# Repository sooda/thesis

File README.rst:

Multi-view stereo reconstruction for computer graphics content capture
======================================================================

Hello, this is my master's thesis work titled as above, and contains both the thesis text itself and some source code and electrical schematics developed during the work in Aalto University in 2014-2015.
For the occasional gibberish, consult a Finnish dictionary.
The technical "multi-view stereo reconstruction" is sometimes called "3D scanning": digitizing real-life object geometry from multiple photographs.
The practical work in this thesis was about building a rig for that purpose.
No reconstruction programs were written, unfortunately.
Try e.g. VisualSFM_ and MeshLab_ for that.

.. _VisualSFM: http://ccwu.me/vsfm/
.. _MeshLab: http://meshlab.sourceforge.net/

.. image:: latex/gfx/bitmap/setupcams.jpg
   :width: 500px
   :alt: camera array

.. image:: latex/gfx/bitmap/horsereconst.jpg
   :width: 500px
   :alt: horse mask rendering

Code
----

The thesis talks also about the background math, but the only code here is for controlling DSLRs remotely using gPhoto2_ in C++ and some shell scripts.
The tools were only tested using nine Canon EOS 700D cameras; no guarantees are given for others, but not much major changes are expected to be required.
I forgot to run valgrind on the final tool, so expect no warranty in memory leaks or any other errors.

.. _gPhoto2: http://gphoto.org/

The code here represents a prototype only, but it works for what was required, it's just not very polished.
I wrote a C++ wrapper for gphoto that is unimaginatively called *gpwrap*.
A preview tool (*gphotogrid*) downloads a live stream from each camera in parallel and allows the user to configure their parameters (aperture and such), with no significant performance optimizations or anything, as it's just a proof of concept.
The wrapper and the grid have been tested to work in recent versions of Linux and Mac OS X using the EOS 700Ds, but YMMV.
A more polished tool called `CaptureQuick`_ is developed on top of it by Daniel Thul; if you are going to use the wrapper for developing your own programs, or want the grid tool, look there too.
CaptureQuick still uses the wrapper written by me with only minor modifications (as of June 2015).
Expect it to grow further.

.. _CaptureQuick: https://github.com/dthul/capture-quick

.. image:: latex/gfx/bitmap/gphotogrid.png
   :width: 500px
   :alt: gphotogrid

Electronics
-----------

I built a simple remote tool for controlling the shutters of the nine cameras via a single usb-serial connection, in `arbitrary order`_ (typically simultaneously, though).
The control output goes directly to the 700Ds' shutter release inputs (a 2.5mm stereo jack).
The box has also a button for human interaction, and it's based on Nucleo-F401RE_, a simple STM32 board.
The schematics and the PCB are in EAGLE_ 7.0.0 format.
I named the thing *camsremote*.
No warranty.

.. _arbitrary order: https://www.youtube.com/watch?v=bDDnQzyOaFg
.. _Nucleo-F401RE: http://www.st.com/nucleoF401RE-pr
.. _EAGLE: http://www.cadsoftusa.com/eagle-pcb-design-software/

.. image:: latex/gfx/bitmap/camsremote.jpg
   :width: 500px
   :alt: remote trigger tool

Abstract
--------

Rendering of photorealistic models is becoming increasingly feasible and important in computer graphics.
Due to the high amount of work in creating such models by hand, required by the need of high level of detail in geometry, colors, and animation, it is desirable to automate the model creation.
This task is realised by recovering content from photographs that describe the modeled subject from multiple viewpoints.
In this thesis, elementary theory on image acquisition and photograph-based reconstruction of geometry and colors is studied and recent research and software for graphics content reconstruction are reviewed.
Based on the studied background, a rig is built as a grid of nine off-the-shelf digital cameras, a custom remote shutter trigger, and supporting software.
The purpose of the rig is to capture high-quality photographs and video in a reliable and practical manner, to be processed in multi-view reconstruction programs.

The camera rig was configured to shoot small static subjects for experiments.
The resulting photos and video were then processed directly for the subject's geometry and color, with little or no image enhancements done.
Two typical reconstruction software pipelines were described and tested.
The rig was found to perform well for several subjects with little subject-specific tuning;
issues in the setup were analyzed and further improvements suggested based on the captured test models.
Image quality of the cameras was found to be excellent for the task, and most problems arose from uneven lighting and practical issues.
The developed rig was found to produce sub-millimeter scale accuracy in geometry and texture of subjects such as human faces.
Future work was suggested for lighting, video synchronization and study of state-of-the-art image processing and reconstruction algorithms.

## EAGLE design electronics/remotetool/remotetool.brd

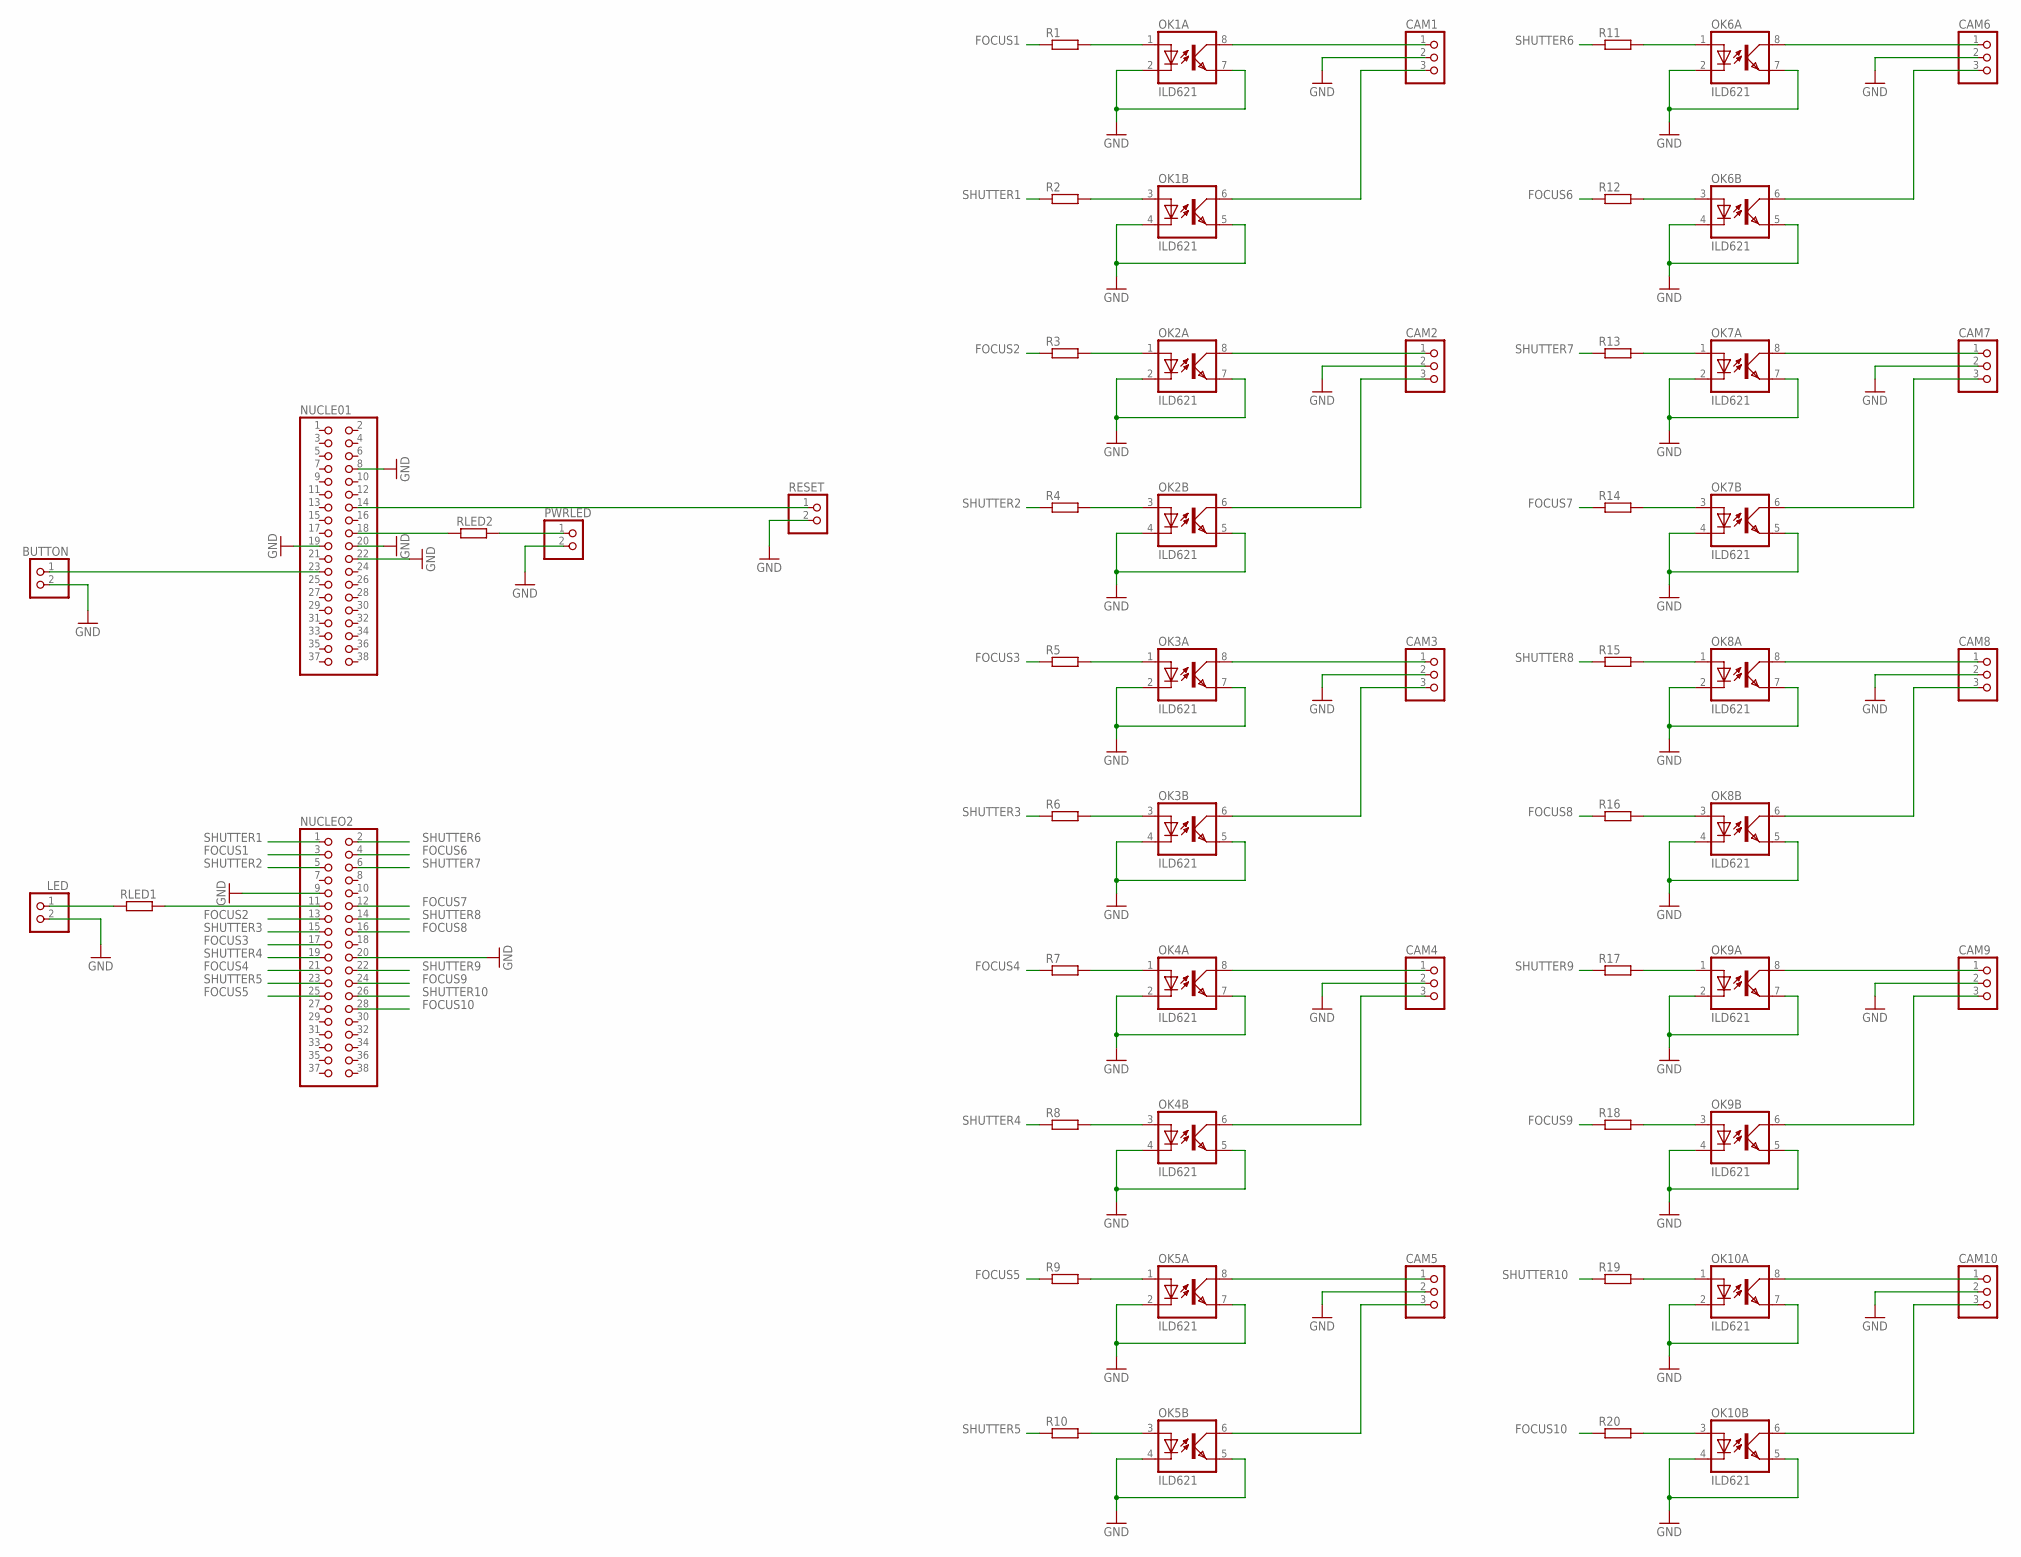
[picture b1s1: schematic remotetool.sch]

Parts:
BUTTON: PINHD-1X2; 1X02
CAM1, CAM2, CAM3, CAM4, CAM5, CAM6, CAM7, CAM8, CAM9, CAM10: PINHD-1X3; 1X03
LED: PINHD-1X2; 1X02
NUCLE01: PINHD-2X19; 2X19
NUCLEO2: PINHD-2X19; 2X19
OK1, OK2, OK3, OK4, OK5, OK6, OK7, OK8, OK9, OK10: ILD621; DIL08
PWRLED: PINHD-1X2; 1X02
R1, R2, R3, R4, R5, R6, R7, R8, R9, R10, R11, R12, R13, R14, R15, R16, R17, R18, R19, R20: R-EU_0207/2V; 0207/2V
RESET: PINHD-1X2; 1X02
RLED1, RLED2: R-EU_0207/2V; 0207/2V

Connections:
FOCUS1: NUCLEO2.3, R1.1
FOCUS2: NUCLEO2.13, R3.1
FOCUS3: NUCLEO2.17, R5.1
FOCUS4: NUCLEO2.21, R7.1
FOCUS5: NUCLEO2.25, R9.1
FOCUS6: NUCLEO2.4, R12.1
FOCUS7: NUCLEO2.12, R14.1
FOCUS8: NUCLEO2.16, R16.1
FOCUS9: NUCLEO2.24, R18.1
FOCUS10: NUCLEO2.28, R20.1
GND: BUTTON.2, CAM1.2, CAM2.2, CAM3.2, CAM4.2, CAM5.2, CAM6.2, CAM7.2, CAM8.2, CAM9.2, CAM10.2, LED.2, NUCLE01.8, NUCLE01.19, NUCLE01.20, NUCLE01.22, NUCLEO2.9, NUCLEO2.20, OK1.2 (C), OK1.4 (C), OK1.5 (EMIT), OK1.7 (EMIT), OK2.2 (C), OK2.4 (C), OK2.5 (EMIT), OK2.7 (EMIT), OK3.2 (C), OK3.4 (C), OK3.5 (EMIT), OK3.7 (EMIT), OK4.2 (C), OK4.4 (C), OK4.5 (EMIT), OK4.7 (EMIT), OK5.2 (C), OK5.4 (C), OK5.5 (EMIT), OK5.7 (EMIT), OK6.2 (C), OK6.4 (C), OK6.5 (EMIT), OK6.7 (EMIT), OK7.2 (C), OK7.4 (C), OK7.5 (EMIT), OK7.7 (EMIT), OK8.2 (C), OK8.4 (C), OK8.5 (EMIT), OK8.7 (EMIT), OK9.2 (C), OK9.4 (C), OK9.5 (EMIT), OK9.7 (EMIT), OK10.2 (C), OK10.4 (C), OK10.5 (EMIT), OK10.7 (EMIT), PWRLED.2, RESET.2
unnamed: OK1.1 (A), R1.2
unnamed: OK1.3 (A), R2.2
unnamed: CAM1.1, OK1.8 (COL)
unnamed: CAM1.3, OK1.6 (COL)
unnamed: OK2.1 (A), R3.2
unnamed: OK2.3 (A), R4.2
unnamed: CAM2.1, OK2.8 (COL)
unnamed: CAM2.3, OK2.6 (COL)
unnamed: OK3.1 (A), R5.2
unnamed: OK3.3 (A), R6.2
unnamed: CAM3.1, OK3.8 (COL)
unnamed: CAM3.3, OK3.6 (COL)
unnamed: OK4.1 (A), R7.2
unnamed: OK4.3 (A), R8.2
unnamed: CAM4.1, OK4.8 (COL)
unnamed: CAM4.3, OK4.6 (COL)
unnamed: OK5.1 (A), R9.2
unnamed: OK5.3 (A), R10.2
unnamed: CAM5.1, OK5.8 (COL)
unnamed: CAM5.3, OK5.6 (COL)
unnamed: OK6.1 (A), R11.2
unnamed: OK6.3 (A), R12.2
unnamed: CAM6.1, OK6.8 (COL)
unnamed: CAM6.3, OK6.6 (COL)
unnamed: OK7.1 (A), R13.2
unnamed: OK7.3 (A), R14.2
unnamed: CAM7.1, OK7.8 (COL)
unnamed: CAM7.3, OK7.6 (COL)
unnamed: OK8.1 (A), R15.2
unnamed: OK8.3 (A), R16.2
unnamed: CAM8.1, OK8.8 (COL)
unnamed: CAM8.3, OK8.6 (COL)
unnamed: OK9.1 (A), R17.2
unnamed: OK9.3 (A), R18.2
unnamed: CAM9.1, OK9.8 (COL)
unnamed: CAM9.3, OK9.6 (COL)
unnamed: OK10.1 (A), R19.2
unnamed: OK10.3 (A), R20.2
unnamed: CAM10.1, OK10.8 (COL)
unnamed: CAM10.3, OK10.6 (COL)
unnamed: NUCLEO2.11, RLED1.2
unnamed: BUTTON.1, NUCLE01.23
unnamed: NUCLE01.14, RESET.1
unnamed: LED.1, RLED1.1
unnamed: NUCLE01.18, RLED2.2
unnamed: PWRLED.1, RLED2.1
SHUTTER1: NUCLEO2.1, R2.1
SHUTTER2: NUCLEO2.5, R4.1
SHUTTER3: NUCLEO2.15, R6.1
SHUTTER4: NUCLEO2.19, R8.1
SHUTTER5: NUCLEO2.23, R10.1
SHUTTER6: NUCLEO2.2, R11.1
SHUTTER7: NUCLEO2.6, R13.1
SHUTTER8: NUCLEO2.14, R15.1
SHUTTER9: NUCLEO2.22, R17.1
SHUTTER10: NUCLEO2.26, R19.1

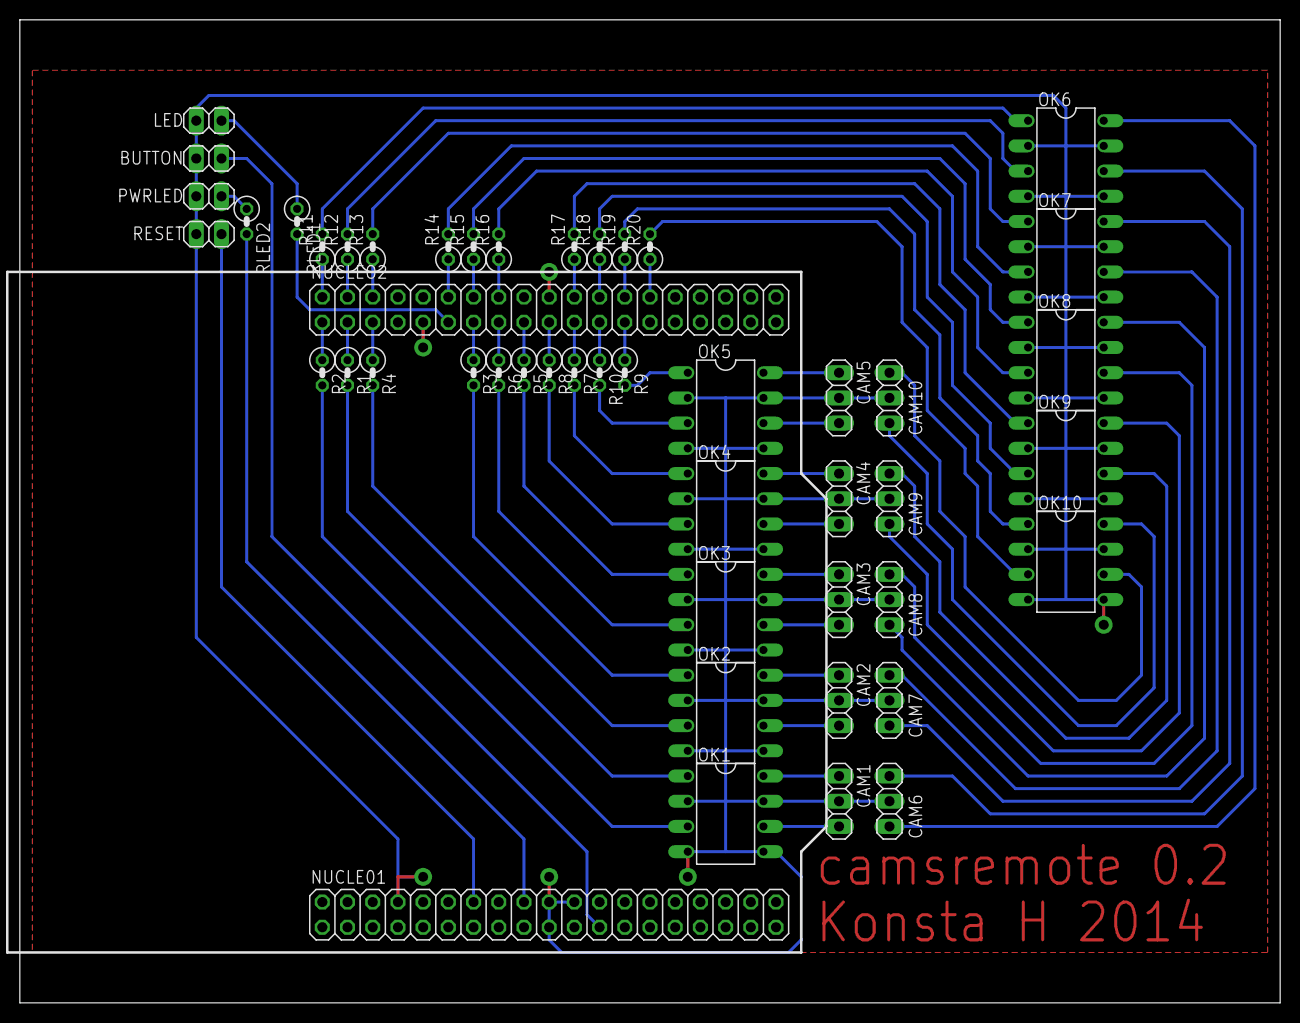
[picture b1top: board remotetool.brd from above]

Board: 2 copper layers, 127.0 x 99.1 mm, 48 parts (0 on the bottom side), 67 nets.

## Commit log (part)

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2014-01-14 initial commit
    Basic modular structure based on the aalto thesis template.
2014-01-31 notes of first three weeks
2014-02-04 opencv example pics, wxwidgets testing to display
2014-02-17 initial latex content, note update
2014-04-14 initial seminar work copypasta
2014-04-15 seminar work updates
2014-04-16 a little about video and imaging
2014-04-17 refactor calib/transform sec
2014-04-18 haaaaaaaaands
2014-04-24 last seminar presis tweaks
2014-04-24 kameraostossuunnitelma
2014-05-02 src: list of all cameras from gphoto
2014-05-02 src: gphoto grid previewer
2014-05-02 gpgrid: also shutter speed slider
2014-05-02 gpwrap: also test iso
2014-05-02 gpgrid: optionspanel hifi; text and padding
2014-05-05 gpgrid: timeline control
    sweet tracks of points on a scrollable and zoomable timeline
2014-05-06 gprid: timeline autoscrolling to follow insertions
2014-05-08 gpgrid: numcams() for app
    no more cams.size() sprinkled randomly everywhere
2014-05-09 gpgrid: change optionspanel wxsliders to wxchoices
    because text in a dropdown list is much better
2014-05-09 gpwrap: remember timeline follow when reseting it
    slight bugfix for when new cameras resets the timeline
2014-05-16 kamerajalustojen ostoslistamuistiinpanot
2014-05-24 tex: light refactor, initial implementation text
2014-05-24 tex: imaging, pinhole from seminar work
    copy pasta. need to clarify the weak perspective stuff, matrices and
    actual matrix use in reprojection, and move the coord sys stuff here.
    gotta learn vim folds. long files are no problem if navigation is
    simple, lots of smaller files are more of a problem.
    like:
    section{sectname} % {{{
2014-05-27 src: shutter lag measurement
    hot shoe connects the middle pin to ground. use pull-up resistor and
    wait for falling edge, timing the delay between shutter release button
    and flash.
    eos 700D: ~76 ms for full f/1.8 aperture, same for f/10, ~79 ms for f/22
2014-05-27 src: tether: messing around with gphoto2 scripts
2014-05-27 tex: shutter text sync
    syncing with flashes, compare to continuous light; light sensor for film
    cameras, ISO speed, lag not so important if consistent among cameras,
    video goes elsewhere
2014-05-27 tex: image download sync
    could calculate max theoretical fps for big uncompressed images
2014-05-27 tex: hw sync
    hardware subsection in background theory might not be necessary as much
    of it is already discussed before
2014-05-28 tex: coord systems and transforms sync
    this section should mabe be renamed, and the intrinsic parameters should
    be moved to the pinhole section and only reviewed here quickly.
    pictures needed too to clarify.
    also add folds to previous forgotten sections.
2014-05-28 tex: normalization sync
    this section is quite disconnected, maybe merge to another somewhere? or
    write a more general section about common background on calibration?
2014-05-28 tex: epipolar geometry sync
    work in this part needs matrices and coordinate change illustrations
2014-05-28 tex: final mvs sync
    multi-view (n-view?) stereo needs much more content and description on
    what exactly needs to be done and how is it related to stereo. trifocal
    tensor instead of matrix etc.
    bundle adjustment is done by many tools (visualsfm etc.), should
    describe that in more detail.
    error metrics are important.
2014-06-02 tex: tracking and face something sync
    maybe cover tracking only quickly and produce a simple proof of concept,
    does not quite fit in
2014-06-02 src: asus xtion note
    i found a kinect clone in a storage shelf
2014-06-03 mbed: led pwm for video record testing
    rolling shutter and canon's video shutter speed are strange
    in the 1/4000 to 1/1000 range, the cam behaves as expected with a
    rolling shutter effect; with a longer exposure, it looks kind of like
    several frames would be taken one after another.
2014-06-05 src: automatic flashtiming computations
    move flashtiming.txt to src and add some ffmpeg and opencv madness for
    auto subframe time detection; audio matching manually in audacity.
2014-06-09 farnell-ostoslista muistiin tännekin
    näiden lisäksi testinä ledejä ja parit vastukset ja iso kasa piuhaa sekä
    tietty optoerottimet, tlp621-2
2014-06-11 tex: instructor meeting notes on thesis structure
2014-06-11 tex: intro refactor
    remove redundant copypasta that came from other places and clean up a
    bit; still utter nonsense.
2014-06-13 tex: compile raddist as a separate pdf for speed
    pdflatex it separately before main pdf
2014-06-17 tex: image download, wip
    work in progress on approximate image size calculations, file formats,
    video mode and stuff
2014-06-18 tex: video text
    initial stuff for video section. needs more pictures. interlace tearing?
2014-06-23 tex: initial brdf diagram from wikipedia (png)
2014-06-24 tex: interlace: black line color, off-by-1 fixes
2014-06-25 tex: draft watermark to each page
2014-06-26 mbed: more controllable pcshot; cycle repeater
    make both focus and shutter buttons fully controllable from pc, like:
    Fabcdefghijk
    Sabcdefghijk
    where a-j are per-camera button bits, 0 or 1.
    R resets everything.
    Python stuff repeats same set for several cameras or cycles all cameras
2014-06-26 tether: add 700d config lists
    manual mode does not have recording destination (it's disabled); in
    video mode it has choices for card and none.
    video mode lacks evfmode, focus mode, metering mode, and auto exposure
    bracketing.
2014-07-02 tether: add 700d moviemode liveview configs
    differs from normal mode at least in available shutter speeds
2014-07-02 tether: update README to contain new files
    this should be kept up to date with all commits, doh
2014-07-02 tether: remove multiconv, just use xargs instead
    the script got only occasional random use.
    ls | xargs -n1 -P4 -IX convert X -resize foo thum/X
2014-07-03 gphoto: do all apps on "make all"
2014-07-03 gpwrap: save_file() cruft cleanup
2014-07-03 gphoto: refactor sigint handler out
2014-07-03 paraphotos: cleanup, document, add -v arg parsing
    wow such complete program
2014-07-03 paraphotos: implement renumbering files
    consistent image numbers between all cameras, starting from 1
2014-07-03 gpwrap: add note on freeing camera abilities
    port info list and camera abilities list are alive kind of during the
    whole program lifetime and are allocated only once, but maybe they
    should be cleaned up to e.g. Context so that it could free them finally.
2014-07-04 gpwrap: use GP_NEW_UNIQUE for local variables
    hmh, there was just a few of them. probably use unique_ptrs for members
    too; gotta think gp's reference counting.
2014-07-04 gpwrap: point to root widgets in gp::Widget
    point to root instead of parent because the parent info is unnecessary
    and root is actually saved to the camera.
    add some notes on widget refcount usage.
2014-07-04 gpwrap: don't write messages on a new line
2014-07-04 tether: let ufraw-batch handle parallelism
    ufraw-batch actually runs the conversion on all cores, so don't xargs
2014-07-16 gpwrap: add move assignment to camera
    move assignment enables e.g. sorting a vector and is meaningful in other
    ways too, doh.
    this needs the context reference member to be a pointer instead, so
    change it too.
2014-07-16 gphotogrid: render camera names in pics
2014-07-16 gpwrap: protect from too few camera names
2014-07-16 gpwrap: makefile: reorder for build directory
    write temp stuff (.o, .d) to a separate directory as they start to
    clutter things up a little.
2014-07-22 prototype for canon remote tool schema and board
    no more hazard dangling wires and breadboard: implement schematics and
    pcb for the wired multi-camera remote shutter controller as an eagle
    project. fits snugly in a used aluminium case found randomly in AS
    electronics lab.
2014-07-23 remotetool: rename second half as it should be
    The second half of connectors is kind of mirrored from the optocoupler
    point of view; rename signals so that all connectors are facing the same
    way when installing. Also make the borrom row labels readable.
2014-07-23 remotetool: rearrange schematic by board
    move the optos around so that their order matches with the physical
    connectors, reducing confusion.
2014-07-23 mbed: pcshot: add inter-shot delay configuration
    an additional delay when the last camera has finished before the first
    starts the next round again
2014-07-23 mbed: pcshot: add 10th pin
    the new hardware just has one more
2014-07-24 mbed: pcshot: add debounce after focus button
    the new pushbuttons on the case are very bouncy and would trigger
    shutters almost every time
2014-07-24 remotetool: add photo of breadboard prototype
2014-07-28 tex: fix camsremote.jpg exif data
    one dot per inch, wat?
2014-07-29 tex: more white watermark color
2014-07-30 tex: initial sfm stuff, not that complicated yet
2014-08-04 tex: iterate 3d background
2014-08-06 pcshot.py: unify repeat and cycle; use argparse
2014-08-11 src: troubleshooting notes for canon cams
2014-08-13 tex: reorganise gfx by file category
    easier makefile at least
2014-08-14 tex: initial conclusion notes
2014-08-14 gitignore: skip latex converted pdf from eps
2014-08-15 tex: dof coc drawings
2014-08-15 tex: implementation details on code
2014-08-17 tex: redraw interlace pic, show also tearing
2014-08-18 tex: tiny fixes in video section
2014-08-23 tex: software googling
2014-08-24 tex: arto's forehead wrinkles
2014-08-25 tex: slight changes in software survey
    note: the programs should be tested to actually talk about them, and the
    algorithms behind them are unknown and proprietary.
2014-08-26 tex: merge some browser tab notes
2014-08-27 tex: clean up camera background until video
2014-08-28 tex: strip camera info from bg to impl
2014-08-28 tex: 3d reconstruction section iteration
    - reiterate text content
    - convert some pics to separate pdfs for clarity
    multi view section needs much love and content (mostly references),
    in other places the scope is starting to get a finished shape
2014-08-29 tex: slight motion cleanup
2014-09-01 tex: labels for dof pic
    oh tikz you are painful and wonderful
2014-09-02 tex: camera comparison tuning
    \paragraphs and some small changes
2014-09-04 tex: tiny fixes in 3d background; add some images
2014-10-19 tex: some old notes of last weeks
2014-10-21 tex: proper pics of the system, lighting impl
2014-10-25 tex: software list references
2014-10-28 gpgrid: compile with optimizations
    why didn't i set this as default? hax it manually off when need to gdb.
2014-11-01 tex: result pictures and some relevant text
2014-11-02 tex: some initial conclusion thoughts
2014-11-05 tex: rotate fan pics 90 degrees and squeeze them
2014-11-05 tex: appendix on hw list and multitrigger uptodate
2014-11-06 presentation: final last night changes
2014-11-06 presentation: talk thoughts as a side help
2014-11-07 tex: background: reword surfaces in cg
2014-11-07 tex: target date, guess professorship codes
2014-11-07 tex: reconstruction: small typofixes etc
2014-11-09 tex: use centering, not center, in figures
    so that's why they took so much space
    http://tex.stackexchange.com/questions/2651/should-i-use-center-or-centering-for-figures-and-tables
2014-11-09 tex: massive citation reiteration
    references, bitches
2014-11-09 tex: preface template
2014-11-11 tex: remove draft watermark, it sucks
    this would be cool so that draft versions wouldn't get mixed up but it
    makes the text kind of difficult to read
2014-11-12 tex: clarify and restructure intro
    get more to the point and describe motivation in a more explicit way.
    also some rewordings.
2014-11-12 tex: mention mac os x problems
2015-05-10 tex: argh first supervisor draft version
    big messy megacommit, blahh
    - style changes like i.e. -> i.e., etc.
    - pic for digital image intro
    - citation reorganization
    - float placement
    - abstract
2015-05-10 tex: tidy up references
    cleanup mistakes in the generated bibtex and cut urls at a hyphen
2015-05-12 tex: slightly more accurate epipolarity
2015-05-14 tex: real pics of distortion, use better symbols
    cliché brick wall barrel distortion illustration.
    kappa and rho are closer to k and p used in other works but reserved
    here.
2015-05-14 tex: remove this random appendices line
    \appendix is enough
2015-05-15 tex: fix software lists and mvs descriptions
    tell just enough about what is different in those. and other small fixes
2015-05-16 tex: hyphenate abstract manually because latex
    latex or aaltothesis.sty doesn't like adding finnish there too, so fix
    the hyphenation manually where necessary (even though it might get
    rewritten)
2015-05-18 tex: final fixes
    fix some clumsy parts after having read through the whole thing, reorder
    images a bit and add actually 360-degree-pics of the statue model
